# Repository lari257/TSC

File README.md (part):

### Florea Larisa - 333CA

# eBook Reader

## Diagrama Bloc

[Diagrama](https://www.mermaidchart.com/raw/8d10b74d-7767-4ccb-a096-3764c8156505?theme=light&version=v0.1&format=svg)

## Bill Of Materials (BOM)

| Part         | Value                         | Device                                     | Footprint Name                          | Detailed Description                                                                                                                   | CHECK_PRICES                                                                                                            | DATASHEET                                                                                                                   |
|--------------|-------------------------------|--------------------------------------------|-----------------------------------------|----------------------------------------------------------------------------------------------------------------------------------------|-------------------------------------------------------------------------------------------------------------------------|------------------------------------------------------------------------------------------------------------------------------|
| C1           | 4.7uF                         | EAGLE-LTSPICE_CC0402                         | EAGLE-LTSPICE_C0402                         | CAPACITOR, European symbol                                                                                                             | [Link](https://ro.mouser.com/ProductDetail/EPCOS-TDK/B72520T0350K062?qs=dEfas%2FXlABIszF52uu7vrg%3D%3D)                                                                                                                     | nan                                                                                                                          |
| C1_BAT2      | 4.7uF                         | EAGLE-LTSPICE_CC0402                         | EAGLE-LTSPICE_C0402                         | CAPACITOR, European symbol                                                                                                             | [Link](https://ro.mouser.com/ProductDetail/EPCOS-TDK/B72520T0350K062?qs=dEfas%2FXlABIszF52uu7vrg%3D%3D)                                                                                                                       | nan                                                                                                                          |
| C2           | 100nF                         | ESP32_WROVER_EAGLE-LTSPICE_CC0402            | ESP32_WROVER_EAGLE-LTSPICE_C0402            | CAPACITOR, European symbol                                                                                                             | [Link](https://componentsearchengine.com/part-view/CC0402MRX5R5BB106/YAGEO)                                                                                                                    | nan                                                                                                                          |
| C2_BAT      | 4.7uF                         | ESP32_WROVER_EAGLE-LTSPICE_CC0402            | ESP32_WROVER_EAGLE-LTSPICE_C0402            | CAPACITOR, European symbol                                                                                                             | [Link](https://componentsearchengine.com/part-view/CC0402MRX5R5BB106/YAGEO)                                                                                                                      | nan                                                                                                                          |
| C3           | 100uF TANT                    | RCL_CPOL-EUCT3528                          | RCL_CT3528                          | POLARIZED CAPACITOR, European symbol                                                                                                   | [Link](https://eu.mouser.com/ProductDetail/KYOCERA-AVX/F910J107MBAAJ6?qs=PqoDHHvF649LraCA%2FjeGXg%3D%3D)                        | [datasheet](https://ro.mouser.com/datasheet/2/40/F91_AJ6-3162641.pdf)                                                                     |
| C4           | 4.7uF/25V                     | ESP32_WROVER_EAGLE-LTSPICE_CC0402            | ESP32_WROVER_EAGLE-LTSPICE_C0402            | CAPACITOR, European symbol                                                                                                             | [Link](https://componentsearchengine.com/part-view/CC0402MRX5R5BB106/YAGEO)                                                                                                                      | nan                                                                                                                          |
| C4_USB       | 100nF                         | ESP32_WROVER_EAGLE-LTSPICE_CC0402            | ESP32_WROVER_EAGLE-LTSPICE_C0402            | CAPACITOR, European symbol                                                                                                             | [Link](https://componentsearchengine.com/part-view/CC0402MRX5R5BB106/YAGEO)                                                                                                                      | nan                                                                                                                          |
| C5           | 1uF                           | ESP32_WROVER_EAGLE-LTSPICE_CC0402            | ESP32_WROVER_EAGLE-LTSPICE_C0402            | CAPACITOR, European symbol                                                                                                             | [Link](https://componentsearchengine.com/part-view/CC0402MRX5R5BB106/YAGEO)                                                                                                                      | nan                                                                                                                          |
| C5_USB       | 4.7uF                        | ESP32_WROVER_EAGLE-LTSPICE_CC0402            | ESP32_WROVER_EAGLE-LTSPICE_C0402            | CAPACITOR, European symbol                                                                                                             | [Link](https://componentsearchengine.com/part-view/CC0402MRX5R5BB106/YAGEO)                                                                                                                      | nan                                                                                                                          |
| C6           | 100nF                         | ESP32_WROVER_EAGLE-LTSPICE_CC0402            | ESP32_WROVER_EAGLE-LTSPICE_C0402            | CAPACITOR, European symbol                                                                                                             | [Link](https://componentsearchengine.com/part-view/CC0402MRX5R5BB106/YAGEO)                                                                                                                      | nan                                                                                                                          |
| C7           | 10uF                          | ESP32_WROVER_EAGLE-LTSPICE_CC0402            | ESP32_WROVER_EAGLE-LTSPICE_C0402            | CAPACITOR, European symbol                                                                                                             | [Link](https://componentsearchengine.com/part-view/CC0402MRX5R5BB106/YAGEO)                                                                                                                     | nan                                                                                                                          |
| C8           | 100nF                         | ESP32_WROVER_EAGLE-LTSPICE_CC0402            | ESP32_WROVER_EAGLE-LTSPICE_C0402            | CAPACITOR, European symbol                                                                                                             | [Link](https://componentsearchengine.com/part-view/CC0402MRX5R5BB106/YAGEO)                                                                                                                      | nan                                                                                                                          |
| C9           | 100nF                         | EAGLE-LTSPICE_CC0402                         | EAGLE-LTSPICE_C0402                         | CAPACITOR, European symbol                                                                                                             | [Link](https://ro.mouser.com/ProductDetail/EPCOS-TDK/B72520T0350K062?qs=dEfas%2FXlABIszF52uu7vrg%3D%3D)                                                                                                                     | nan                                                                                                                          |
| C10          | 100nF                         | ESP32_WROVER_EAGLE-LTSPICE_CC0402            | ESP32_WROVER_EAGLE-LTSPICE_C0402            | CAPACITOR, European symbol                                                                                                             | [Link](https://componentsearchengine.com/part-view/CC0402MRX5R5BB106/YAGEO)                                                                                                                     | nan                                                                                                                          |
| C10_SUPERCAP | CPH3225A                     | CPH3225A                                   | CAPCP3225X100N                           | Cap 0.011F 3.3V 1210 Flat Check availability                                                                                           | [Link](https://www.snapeda.com/parts/CPH3225A/Seiko+Instruments/view-part/?ref=eda)                                               | [datasheet](https://www.snapeda.com/parts/CPH3225A/Seiko%20Instruments/datasheet/)                                                         |
| CHANGE_BUTTON| BUTTON_CUSYOMV1               | BUTTON_CUSYOMV1                            | MYBUTTON                                | nan                                                                                                                                    | [Link](https://industry.panasonic.com/global/en/products/control/switch/light-touch/number/evqpuj02k)                             | [datasheet](https://industry.panasonic.com/global/en/downloads?tab=catalog&small_g_cd=203&part_no=EVQPUJ02K)                               |
| CHG_LED      | nan                           | ADAFRUIT_LEDCHIP-LED0603                     | ADAFRUIT_CHIP-LED0603                     | LED                                                                                                                                    | [Link](https://www.snapeda.com/parts/KP-1608SURCK/Kingbright/view-part/?ref=eda)                                                 | [datasheet](https://www.snapeda.com/parts/KP-1608SURCK/Kingbright/datasheet/)                                                             |
| C_DELAY      | 100nF                         | ESP32_WROVER_EAGLE-LTSPICE_CC0402            | ESP32_WROVER_EAGLE-LTSPICE_C0402            | CAPACITOR, European symbol                                                                                                             | [Link](https://componentsearchengine.com/part-view/CC0402MRX5R5BB106/YAGEO)                                                                                                                     | nan                                                                                                                          |
| D1           | USBLC6-2SC6Y                  | USBLC6-2SC6Y                               | SOT95P280X145-6N                         | Low Cap. ESD Protection Auto SOT-23-6 STMicroelectronics USBLC6-2SC6Y, Dual Uni-Directional TVS Diode Array, 6-Pin SOT-23             | [Link](https://www.snapeda.com/parts/USBLC6-2SC6Y/STMicroelectronics/view-part/?ref=eda)                                           | [datasheet](https://www.snapeda.com/parts/USBLC6-2SC6Y/STMicroelectronics/datasheet/)                                                     |
| D2           | ESP32_WROVER_AVX---SD0805S020S1R0_AVX_SD0805S020S1R0_0_0AVX_SD0805S020S1R0_0_0 | ESP32_WROVER_AVX---SD0805S020S1R0_AVX_SD0805S020S1R0_0_0AVX_SD0805S020S1R0_0_0 | ESP32_WROVER_AVX---SD0805S020S1R0_AVX_SD0805S020S1R0_0 | Schottky Barrier Rectifier Diode                                                                                                       | [Link](https://eu.mouser.com/ProductDetail/KYOCERA-AVX/SD0805S020S1R0?qs=jCA%252BPfw4LHbpkAoSnwrdjw%3D%3D)                        | [datasheet](http://datasheets.avx.com/schottky.pdf)                                                                                        |
| D3           | MBR0530                       | MBR0530                                    | SOD3716X135N                            | ON SEMICONDUCTOR - MBR0530 - DIODE, SCHOTTKY, 0.5A, 30V, SOD-123                                                                        | [Link](https://eu.mouser.com/ProductDetail/KYOCERA-AVX/SD0805S020S1R0?qs=jCA%252BPfw4LHbpkAoSnwrdjw%3D%3D)                        | [datasheet](https://ro.mouser.com/datasheet/2/40/schottky-3165252.pdf)                                                                    |
| D4           | MBR0530                       | MBR0530                                    | SOD3716X135N                            | ON SEMICONDUCTOR - MBR0530 - DIODE, SCHOTTKY, 0.5A, 30V, SOD-123                                                                        | [Link](https://www.snapeda.com/parts/MBR0530/Onsemi/view-part/?ref=eda)                                                            | [datasheet](https://www.snapeda.com/parts/MBR0530/ON%20Semiconductor/datasheet/)                                                           |
| D5           | MBR0530                       | MBR0530                                    | SOD3716X135N                            | ON SEMICONDUCTOR - MBR0530 - DIODE, SCHOTTKY, 0.5A, 30V, SOD-123                                                                        | [Link](https://www.snapeda.com/parts/MBR0530/Onsemi/view-part/?ref=eda)                                                            | [datasheet](https://www.snapeda.com/parts/MBR0530/ON%20Semiconductor/datasheet/)                                                           |
| D6           | PGB1010603MR                  | PGB1010603MR                               | DIOC1608X36N                            | Check availability                                                                                                                     | [Link](https://www.snapeda.com/parts/PGB1010603MR/Littelfuse/view-part/?ref=eda)                                                   | [datasheet](https://www.snapeda.com/parts/PGB1010603MR/Littelfuse%20Inc./datasheet/)                                                       |
| D7           | ESP32_WROVER_AVX---SD0805S020S1R0_AVX_SD0805S020S1R0_0_0AVX_SD0805S020S1R0_0_0 | ESP32_WROVER_AVX---SD0805S020S1R0_AVX_SD0805S020S1R0_0_0AVX_SD0805S020S1R0_0_0 | ESP32_WROVER_AVX---SD0805S020S1R0_AVX_SD0805S020S1R0_0 | Schottky Barrier Rectifier Diode                                                                                                       | [Link](https://eu.mouser.com/ProductDetail/KYOCERA-AVX/SD0805S020S1R0?qs=jCA%252BPfw4LHbpkAoSnwrdjw%3D%3D)                        | [datasheet](http://datasheets.avx.com/schottky.pdf)                                                                                        |
| D8           | PGB1010603MR                  | PGB1010603MR                               | DIOC1608X36N                            | Check availability                                                                                                                     | [Link](https://www.snapeda.com/parts/PGB1010603MR/Littelfuse/view-part/?ref=eda)                                                   | [datasheet](https://www.snapeda.com/parts/PGB1010603MR/Littelfuse%20Inc./datasheet/)                                                       |
| D9           | PGB1010603MR                  | PGB1010603MR                               | DIOC1608X36N                            | Check availability                                                                                                                     | [Link](https://www.snapeda.com/parts/PGB1010603MR/Littelfuse/view-part/?ref=eda)                                                   | [datasheet](https://www.snapeda.com/parts/PGB1010603MR/Littelfuse%20Inc./datasheet/)                                                       |
| D10          | PGB1010603MR                  | PGB1010603MR                               | DIOC1608X36N                            | Check availability                                                                                                                     | [Link](https://www.snapeda.com/parts/PGB1010603MR/Littelfuse/view-part/?ref=eda)                                                   | [datasheet](https://www.snapeda.com/parts/PGB1010603MR/Littelfuse%20Inc./datasheet/)                                                       |
| D11          | PGB1010603MR                  | PGB1010603MR                               | DIOC1608X36N                            | Check availability                                                                                                                     | [Link](https://www.snapeda.com/parts/PGB1010603MR/Littelfuse/view-part/?ref=eda)                                                   | [datasheet](https://www.snapeda.com/parts/PGB1010603MR/Littelfuse%20Inc./datasheet/)                                                       |
| D12          | PGB1010603MR                  | PGB1010603MR                               | DIOC1608X36N                            | Check availability                                                                                                                     | [Link](https://www.snapeda.com/parts/PGB1010603MR/Littelfuse/view-part/?ref=eda)                                                   | [datasheet](https://www.snapeda.com/parts/PGB1010603MR/Littelfuse%20Inc./datasheet/)                                                       |
| EPD_C1       | 1uF/50V                      | ESP32_WROVER_EAGLE-LTSPICE_CC0402            | ESP32_WROVER_EAGLE-LTSPICE_C0402            | CAPACITOR, European symbol                                                                                                             | [Link](https://componentsearchengine.com/part-view/CC0402MRX5R5BB106/YAGEO)                                                                                                                     | [datasheet](http://datasheets.avx.com/schottky.pdf)                                                                                                                          |
| EPD_C2       | 1uF/50V                      | ESP32_WROVER_EAGLE-LTSPICE_CC0402            | ESP32_WROVER_EAGLE-LTSPICE_C0402            | CAPACITOR, European symbol                                                                                                             | [Link](https://componentsearchengine.com/part-view/CC0402MRX5R5BB106/YAGEO)                                                                                                                     | [datasheet](http://datasheets.avx.com/schottky.pdf)                                                                                                                                                           |
| EPD_C5       | 1uF/50V                      | ESP32_WROVER_EAGLE-LTSPICE_CC0402            | ESP32_WROVER_EAGLE-LTSPICE_C0402            | CAPACITOR, European symbol                                                                                                             | [Link](https://componentsearchengine.com/part-view/CC0402MRX5R5BB106/YAGEO)                                                                                                                     | [datasheet](http://datasheets.avx.com/schottky.pdf)                                                                                                                                |
| EPD_C6       | 1uF/50V                      | ESP32_WROVER_EAGLE-LTSPICE_CC0402            | ESP32_WROVER_EAGLE-LTSPICE_C0402            | CAPACITOR, European symbol                                                                                                             | [Link](https://componentsearchengine.com/part-view/CC0402MRX5R5BB106/YAGEO)                                                                                                                     | [datasheet](http://datasheets.avx.com/schottky.pdf)                                                                                                                                |
| EPD_C7       | 1uF/50V                      | ESP32_WROVER_EAGLE-LTSPICE_CC0402            | ESP32_WROVER_EAGLE-LTSPICE_C0402            | CAPACITOR, European symbol                                                                                                             | [Link](https://componentsearchengine.com/part-view/CC0402MRX5R5BB106/YAGEO)                                                                                                                     | [datasheet](http://datasheets.avx.com/schottky.pdf)                                                                                                                               |
| EPD_C8       | 1uF/50V                      | ESP32_WROVER_EAGLE-LTSPICE_CC0402            | ESP32_WROVER_EAGLE-LTSPICE_C0402            | CAPACITOR, European symbol                                                                                                             | [Link](https://componentsearchengine.com/part-view/CC0402MRX5R5BB106/YAGEO)                                                                                                                     | [datasheet](http://datasheets.avx.com/schottky.pdf)                                                                                                                                |
| EPD_C9       | 1uF/50V                      | ESP32_WROVER_EAGLE-LTSPICE_CC0402            | ESP32_WROVER_EAGLE-LTSPICE_C0402            | CAPACITOR, European symbol                                                                                                             | [Link](https://componentsearchengine.com/part-view/CC0402MRX5R5BB106/YAGEO)                                                                                                                     | [datasheet](http://datasheets.avx.com/schottky.pdf)                                                                                                                                |
| EPD_C10      | 1uF/50V                      | ESP32_WROVER_EAGLE-LTSPICE_CC0402            | ESP32_WROVER_EAGLE-LTSPICE_C0402            | CAPACITOR, European symbol                                                                                                             | [Link](https://componentsearchengine.com/part-view/CC0402MRX5R5BB106/YAGEO)                                                                                                                     | [datasheet](http://datasheets.avx.com/schottky.pdf)                                                                                                                                |
| EPD_C11      | 1uF/50V                      | ESP32_WROVER_EAGLE-LTSPICE_CC0402            | ESP32_WROVER_EAGLE-LTSPICE_C0402            | CAPACITOR, European symbol                                                                                                             | [Link](https://componentsearchengine.com/part-view/CC0402MRX5R5BB106/YAGEO)                                                                                                                     | [datasheet](http://datasheets.avx.com/schottky.pdf)                                                                                                                               |
| EPD_C12      | 1uF/50V                      | ESP32_WROVER_EAGLE-LTSPICE_CC0402            | ESP32_WROVER_EAGLE-LTSPICE_C0402            | CAPACITOR, European symbol                                                                                                             | [Link](https://componentsearchengine.com/part-view/CC0402MRX5R5BB106/YAGEO)                                                                                                                     | [datasheet](http://datasheets.avx.com/schottky.pdf)                                                                                                                                |
| IC1          | BD5229G-TR                   | BD5229G-TR                                 | SOT95P280X125-5N                         | Voltage Detector with Adjustable Delay Time: CMOS reset IC, low current consumption, Nch Open Drain and CMOS output types               | [Link](https://componentsearchengine.com/part-view/BD5229G-TR/ROHM%20Semiconductor)                                                | [datasheet](https://analytics.supplyframe.com/trackingservlet/track/?r=0x34EY99PS_gIu2qWuzU9_U842M9-un2szqNoXX0OQ9lqbiEKGN3BJ73jgvlrgiXR89Peb0evqc4GXoUXllBhmfH5FwctZio74NZjIXK4nzRihNQSXdSI3BytPQ01W2mbDl-BrHnDitFFECll9ZQTojC49rQmJNJKdgEcm3aSYjKEsMXPl-eGs-pMLJ6GfjQ2BiKCrz1Zc4X-qzG_VKV2vSzv5P64Ul7Il20ycllQHFjlUO2yTCSMr3lB_jTotw40hK-OEmTdpXx-FpzhJ86P5OvAlgiTQyMiC4Ffnw4yYxkQBVqaiFBg7qrqEqqVSG5v66qM9MTFYImVZ49_rSfStbzcxZuFs4E34nEuhMtfiKeEXX8C4ukc9Dx9NPlTcXcvuyK8oeiAy2ZaZQDfLPj6QFwce4mx7LCqKQZbV9OYmnvPS6jR1oAjYl8BoXRPWUJ15zMhGiMZbVlex-jQFMXW69CJW_IpZKRdsiNKH4ODU_1sqvLLuSSOT8tdE2JjOemnsC60ps8LwboHBeA2g6oA7NNs5-4F5aeZhiCtD42Z5ROwjQ2LlPtjcLlvpGBeHIItUY6A8k3oFuRSm1vUF3wN8_AuXjXENQ3hBxb6uKJO6IWX4DfXH-rBL1GXdAFk5fJeg6UJ1wtLjiR_lA2QrRxQg) |
| IC4          | XC6220A331MR-G               | XC6220A331MR-G                             | SOT95P280X120-5N                         | LDO Voltage Regulators                                                                                                                 | [Link](https://componentsearchengine.com/part-view/XC6220A331MR-G/Torex)                                                      | [datasheet](https://analytics.supplyframe.com/trackingservlet/track/?r=0x34EY99PS_gIu2qWuzU9_U842M9-un2szqNoXX0OQ9lqbiEKGN3BJ73jgvlrgiXR89Peb0evqc4GXoUXllBhmfH5FwctZio74NZjIXK4nyB_3F6n5b2GpxjFkeCFGxjIjl2pAOVy2zcoQGQxuo036k82aGL63A7iug3M0vDx44b9y4q5Rgkc_UTcoUbz-EFKm35u_Pt-UF5-Qq6wcvjqqlBMb2f4RZCO7jxguRPFrgtzlu-fR4ingqEGNbtkagfpmEwtRP5B3cC8Kbx1BcIGKPYw6AweR1OQe9e4kwHfOX0WSJenm7GAt6qfmRfSkY__Bln0SGRQRi7Gb6appE-It2tLEig19WC7b52EeQQlAWpHibjyTqb00F7pqNazdRJYga1x68e32CNZt8xWLj3NfJVDOHS8ZS42zhawi9DWA1aRL3hvdnRcB352G10IL46169qwDsBVTcBHABUmJOZLUiFPAKnU5dw3RkOVJIhv6hb0GJ6_iu4F4MNWLmP2ofAh9emlLrBRmI1lrzpkKKDvQ) |
| J1           | FH34SRJ-24S-0.5SH_99_         | FH34SRJ-24S-0.5SH_99_                       | FH34SRJ24S05SH99                         | 24 Position FFC, FPC Connector Contacts, Top and Bottom 0.020 (0.50mm) Surface Mount, Right Angle                                    | [Link](https://componentsearchengine.com/part-view/XC6220A331MR-G/Torex)                                                      | [datasheet](https://analytics.supplyframe.com/trackingservlet/track/?r=0x34EY99PS_gIu2qWuzU9_U842M9-un2szqNoXX0OQ9lqbiEKGN3BJ73jgvlrgiXR89Peb0evqc4GXoUXllBhmfH5FwctZio74NZjIXK4nyB_3F6n5b2GpxjFkeCFGxjIjl2pAOVy2zcoQGQxuo036k82aGL63A7iug3M0vDx44b9y4q5Rgkc_UTcoUbz-EFKm35u_Pt-UF5-Qq6wcvjqqlBMb2f4RZCO7jxguRPFrgtzlu-fR4ingqEGNbtkagfpmEwtRP5B3cC8Kbx1BcIGKPYw6AweR1OQe9e4kwHfOX0WSJenm7GAt6qfmRfSkY__Bln0SGRQRi7Gb6appE-It2tLEig19WC7b52EeQQlAVZAmjkjl9RSryO-btGBH9xYga1x68e32CNZt8xWLj3NfJVDOHS8ZS42zhawi9DWA1aRL3hvdnRcB352G10IL46169qwDsBVTcBHABUmJOZLUiFPAKnU5dw3RkOVJIhv6hb0GJ6_iu4F4MNWLmP2ofAh9emlLrBRmI1lrzpkKKDvQ) |
| J2           | SAMACSYS_PARTS_USB4110-GF-A   | SAMACSYS_PARTS_USB4110-GF-A                 | SAMACSYS_PARTS_USB4110GFA                 | CONN USB 2.0 TYPE-C R/A SMT                                                                                                            | [Link](https://componentsearchengine.com/part-view/USB4110-GF-A/GCT%20(GLOBAL%20CONNECTOR%20TECHNOLOGY))                        | [datasheet](https://analytics.supplyframe.com/trackingservlet/track/?r=0x34EY99PS_gIu2qWuzU9_U842M9-un2szqNoXX0OQ9lqbiEKGN3BJ73jgvlrgiXR89Peb0evqc4GXoUXllBhmfH5FwctZio74NZjIXK4nzoCi89ZctA4-kDp3BQhkXpH2DzsdO0BvVNaNDstYgXoJP31ecBQz8TbvXGeDXm6lLlGaktv_ZGcnQDXY_Jm4l7qTzZoYvrcDuK6DczS8PHjvO_sLMu5UeAZ8GC7ci13apB0YMahqYRJzrQKert1kdW90QfLJiqmEa800fLodTIaw6Y6Er8Udb1Qer9oaUT73Q0u_seRB1eNyIOWRehwOBjnt5uE3551K46VPpa8BqQGgL8C7WZ9xB_-wXKErpK07VtbRf3EeHwJSoZTlUkLiK1n4ej5DBFkUkQWc_1u9LdksKwxt-NL4Q595A7224xsugtkbEFPk8oOxSGJ_LHYAQAbZcxjTr7-0B2gfKUc0nIgMhHQ1ZmsU-U87OSIrunF4mGuvL05dMNyqXJqtC-uoX003WGaG4kTFpIgyyEskwr4Y4nNs8v65MrOUj8A-o40EQUWDLttvT4qqUpxJw-bbM4kRSPfo2732k6xYzg6g3hisuczWtyDRXRBbx2AzOqNGhOKW6MmYPiwZBj99pIC-1j) |
| J3           | QWIIC_RIGHT_ANGLE             | QWIIC_CONNECTORJS-1MM                       | JST04_1MM_RA                             | SparkFun I2C Standard Qwiic Connector                                                                                                 | [Link](4208%20Adafruit%20\|%20Mouser)                                                                                   | [datasheet](https://www.armega.com.tr/datasheet/4208-adafruit-industries-llc-datasheet-7323652)                                           |
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
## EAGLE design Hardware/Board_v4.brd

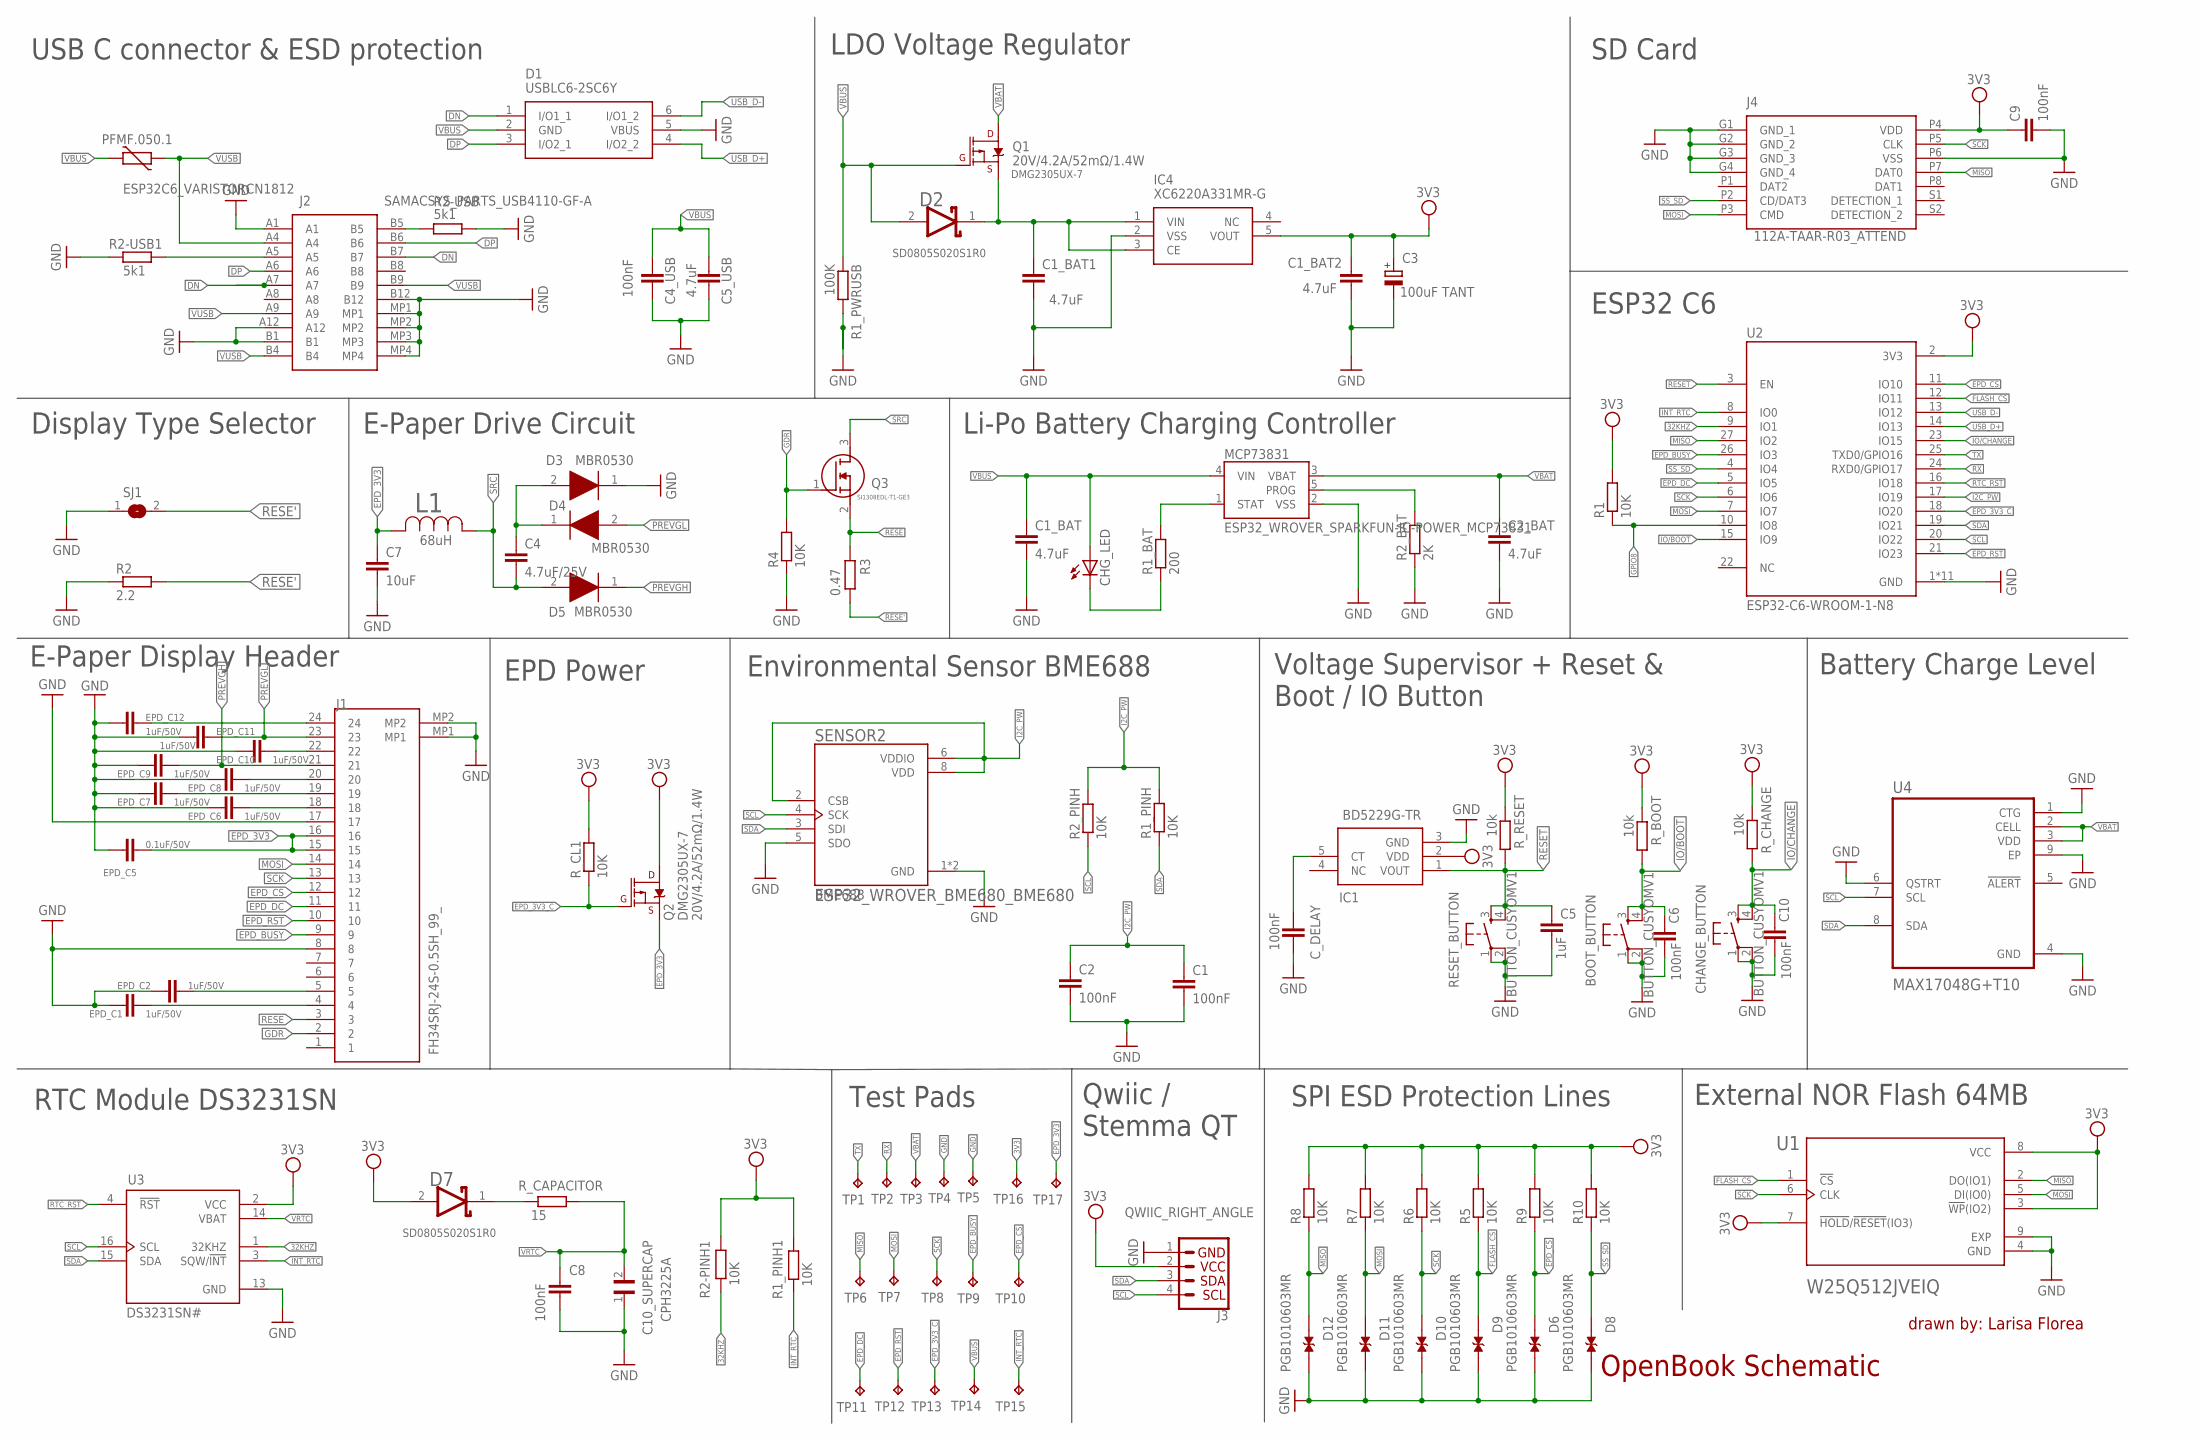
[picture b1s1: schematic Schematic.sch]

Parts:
BOOT_BUTTON: BUTTON_CUSYOMV1; MYBUTTON
C1, C2, C6, C8, C9, C10: 100nF; EAGLE-LTSPICE_C0402
C1_BAT, C2_BAT: 4.7uF; EAGLE-LTSPICE_C0402
C1_BAT1, C1_BAT2, C5_USB: 4.7uF; ESP32_WROVER_EAGLE-LTSPICE_C0402
C3: 100uF TANT; RCL_CT3528
C4: 4.7uF/25V; ESP32_WROVER_EAGLE-LTSPICE_C0402
C4_USB: 100nF; ESP32_WROVER_EAGLE-LTSPICE_C0402
C5: 1uF; EAGLE-LTSPICE_C0402
C7: 10uF; ESP32_WROVER_EAGLE-LTSPICE_C0402
C10_SUPERCAP: CPH3225A; CAPCP3225X100N
CHANGE_BUTTON: BUTTON_CUSYOMV1; MYBUTTON
CHG_LED: ADAFRUIT_LEDCHIP-LED0603; ADAFRUIT_CHIP-LED0603
C_DELAY: 100nF; EAGLE-LTSPICE_C0402
D1: USBLC6-2SC6Y; SOT95P280X145-6N
D2, D7: ESP32_WROVER_AVX---SD0805S020S1R0_AVX_SD0805S020S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; ESP32_WROVER_AVX---SD0805S020S1R0_AVX_SD0805S020S1R0_0
D3, D4, D5: MBR0530; SOD3716X135N
D6, D8, D9, D10, D11, D12: PGB1010603MR; DIOC1608X36N
EPD_C1, EPD_C2, EPD_C6, EPD_C7, EPD_C8, EPD_C9, EPD_C10, EPD_C11, EPD_C12: 1uF/50V; ESP32_WROVER_EAGLE-LTSPICE_C0402
EPD_C5: 0.1uF/50V; ESP32_WROVER_EAGLE-LTSPICE_C0402
IC1: BD5229G-TR; SOT95P280X125-5N
IC4: XC6220A331MR-G; SOT95P280X120-5N
J1: FH34SRJ-24S-0.5SH_99_; FH34SRJ24S05SH99
J2: SAMACSYS_PARTS_USB4110-GF-A; SAMACSYS_PARTS_USB4110GFA
J3: QWIIC_RIGHT_ANGLE; JST04_1MM_RA
J4: 112A-TAAR-R03_ATTEND; 112ATAARR03ATTEND
L1: 744043680IND_4828-WE-TPC_WRE; IND_4828-WE-TPC_WRE
MCP73831: ESP32_WROVER_SPARKFUN-IC-POWER_MCP73831; ESP32_WROVER_SPARKFUN-IC-POWER_SOT23-5
PFMF.050.1: ESP32C6_VARISTORCN1812; ESP32C6_VARISTOR_CT/CN1812
Q1, Q2: 20V/4.2A/52mΩ/1.4W; ESP32_WROVER_SPARKFUN-DISCRETESEMI_SOT23-3
Q3: SI1308EDL-T1-GE3; SOT65P210X110-3N
R1, R1_PINH, R1_PINH1, R2-PINH1, R2_PINH, R4, R5, R6, R7, R8, R9, R10: 10K; ESP32_WROVER_EAGLE-LTSPICE_R0402
R1_BAT: 200; ESP32_WROVER_EAGLE-LTSPICE_R0402
R1_PWRUSB: 100K; ESP32_WROVER_EAGLE-LTSPICE_R0402
R2: 2.2; ESP32_WROVER_EAGLE-LTSPICE_R0402
R2-USB, R2-USB1: 5k1; ESP32_WROVER_EAGLE-LTSPICE_R0402
R2_BAT: 2K; ESP32_WROVER_EAGLE-LTSPICE_R0402
R3: 0.47; ESP32_WROVER_EAGLE-LTSPICE_R0402
RESET_BUTTON: BUTTON_CUSYOMV1; MYBUTTON
R_BOOT: 10k; ESP32_WROVER_EAGLE-LTSPICE_R0402
R_CAPACITOR: 15; ESP32_WROVER_EAGLE-LTSPICE_R0402
R_CHANGE: 10k; ESP32_WROVER_EAGLE-LTSPICE_R0402
R_CL1: 10K; ESP32_WROVER_EAGLE-LTSPICE_R0402
R_RESET: 10k; ESP32_WROVER_EAGLE-LTSPICE_R0402
SENSOR2: ESP32_WROVER_BME680_BME680; ESP32_WROVER_BME680_PSON80P300X300X100-8N
SJ1: SJ
TP1, TP2, TP3, TP4, TP5, TP6, TP7, TP8, TP9, TP10, TP11, TP12, TP13, TP14, TP15, TP16, TP17: TPTP20R; TP20R
U1: W25Q512JVEIQ; SON127P600X800X80-9N
U2: ESP32-C6-WROOM-1-N8; XCVR_ESP32-C6-WROOM-1-N8
U3: DS3231SN#; SOIC127P1032X265-16N
U4: MAX17048G+T10; SON50P200X200X80-9N

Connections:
3V3: C1_BAT2.1, C3.+, C9.1, D7.2 (ANODE), IC1.2 (VDD), IC4.5 (VOUT), J3.2, J4.P4 (VDD), Q2.3 (D), R1.2, R1_PINH1.2, R2-PINH1.2, R5.2, R6.2, R7.2, R8.2, R9.2, R10.2, R_BOOT.1, R_CHANGE.1, R_CL1.2, R_RESET.1, TP16.TP, U1.3 (!WP!(IO2)), U1.7 (!HOLD!/!RESET!(IO3)), U1.8 (VCC), U2.2 (3V3), U3.2 (VCC)
32KHZ: R2-PINH1.1, U2.9 (IO1), U3.1 (32KHZ)
DN: D1.1 (I/O1_1), J2.A7, J2.B7
DP: D1.3 (I/O2_1), J2.A6, J2.B6
EPD_3V3: C7.1, EPD_C5.1, J1.15, J1.16, L1.2, Q2.2 (S), TP17.TP
EPD_3V3_C: Q2.1 (G), R_CL1.1, TP13.TP, U2.18 (IO20)
EPD_BUSY: J1.9, TP9.TP, U2.26 (IO3)
EPD_CS: D6.1, J1.12, R9.1, TP10.TP, U2.11 (IO10)
EPD_DC: J1.11, TP11.TP, U2.5 (IO5)
EPD_RST: J1.10, TP12.TP, U2.21 (IO23)
FLASH_CS: D9.1, R5.1, U1.1 (!CS), U2.12 (IO11)
GDR: J1.2, Q3.1 (G), R4.2
GND: BOOT_BUTTON.1, BOOT_BUTTON.2, C1.2, C1_BAT.2, C1_BAT1.2, C1_BAT2.2, C2.2, C2_BAT.2, C3.-, C4_USB.2, C5.2, C5_USB.2, C6.2, C7.2, C8.2, C9.2, C10.2, C10_SUPERCAP.1, CHANGE_BUTTON.1, CHANGE_BUTTON.2, C_DELAY.2, D1.5 (VBUS), D3.1 (K), D6.2, D8.2, D9.2, D10.2, D11.2, D12.2, EPD_C1.2, EPD_C2.2, EPD_C5.2, EPD_C6.2, EPD_C7.2, EPD_C8.2, EPD_C9.2, EPD_C10.2, EPD_C11.2, EPD_C12.2, IC1.3 (GND), IC4.2 (VSS), J1.8, J1.17, J1.MP1, J1.MP2, J2.A1, J2.A12, J2.B1, J2.B12, J2.MP1, J2.MP2, J2.MP3, J2.MP4, J3.1, J4.G1 (GND_1), J4.G2 (GND_2), J4.G3 (GND_3), J4.G4 (GND_4), J4.P6 (VSS), MCP73831.2 (VSS), R1_PWRUSB.2, R2.1, R2-USB.2, R2-USB1.1, R2_BAT.1, R4.1, RESET_BUTTON.1, RESET_BUTTON.2, SENSOR2.1 (GND), SENSOR2.5 (SDO), SENSOR2.7 (GND), SJ1.1, TP4.TP, TP5.TP, U1.4 (GND), U1.9 (EXP), U2.1 (GND), U2.28 (GND), U2.29_1 (GND), U2.29_2 (GND), U2.29_3 (GND), U2.29_4 (GND), U2.29_5 (GND), U2.29_6 (GND), U2.29_7 (GND), U2.29_8 (GND), U2.29_9 (GND), U3.13 (GND), U4.1 (CTG), U4.4 (GND), U4.6 (QSTRT), U4.9 (EP)
GPIO8: R1.1, U2.10 (IO8)
I2C_PW: C1.1, C2.1, R1_PINH.2, R2_PINH.2, SENSOR2.2 (CSB), SENSOR2.6 (VDDIO), SENSOR2.8 (VDD), U2.17 (IO19)
INT_RTC: R1_PINH1.1, TP15.TP, U2.8 (IO0), U3.3 (SQW/!INT)
IO/BOOT: BOOT_BUTTON.3, BOOT_BUTTON.4, C6.1, R_BOOT.2, U2.15 (IO9)
IO/CHANGE: C10.1, CHANGE_BUTTON.3, CHANGE_BUTTON.4, R_CHANGE.2, U2.23 (IO15)
MISO: D12.1, J4.P7 (DAT0), R8.1, TP6.TP, U1.2 (DO(IO1)), U2.27 (IO2)
MOSI: D11.1, J1.14, J4.P3 (CMD), R7.1, TP7.TP, U1.5 (DI(IO0)), U2.7 (IO7)
unnamed: J2.A5, R2-USB1.2
unnamed: J2.B5, R2-USB.1
unnamed: C1_BAT1.1, D2.1 (CATHODE), IC4.1 (VIN), IC4.3 (CE), Q1.2 (S)
unnamed: CHG_LED.C, R1_BAT.1
unnamed: MCP73831.1 (STAT), R1_BAT.2
unnamed: C4.1, D3.2 (A), D4.1 (K)
unnamed: MCP73831.5 (PROG), R2_BAT.2
unnamed: C_DELAY.1, IC1.5 (CT)
unnamed: D7.1 (CATHODE), R_CAPACITOR.1
unnamed: EPD_C12.1, J1.24
unnamed: EPD_C6.1, J1.18
unnamed: EPD_C7.1, J1.19
unnamed: EPD_C8.1, J1.20
unnamed: EPD_C10.1, J1.22
unnamed: EPD_C2.1, J1.5
unnamed: EPD_C1.1, J1.4
PREVGH: D5.1 (K), EPD_C9.1, J1.21
PREVGL: D4.2 (A), EPD_C11.1, J1.23
RESE: J1.3, Q3.2 (S), R3.2
RESE': R2.2, R3.1, SJ1.2
RESET: C5.1, IC1.1 (VOUT), RESET_BUTTON.3, RESET_BUTTON.4, R_RESET.2, U2.3 (EN)
RTC_RST: U2.16 (IO18), U3.4 (!RST)
RX: TP2.TP, U2.24 (RXD0/GPIO17)
SCK: D10.1, J1.13, J4.P5 (CLK), R6.1, TP8.TP, U1.6 (CLK), U2.6 (IO6)
SCL: J3.4, R2_PINH.1, SENSOR2.4 (SCK), U2.20 (IO22), U3.16 (SCL), U4.7 (SCL)
SDA: J3.3, R1_PINH.1, SENSOR2.3 (SDI), U2.19 (IO21), U3.15 (SDA), U4.8 (SDA)
SRC: C4.2, D5.2 (A), L1.1, Q3.3 (D)
SS_SD: D8.1, J4.P2 (CD/DAT3), R10.1, U2.4 (IO4)
TX: TP1.TP, U2.25 (TXD0/GPIO16)
USB_D+: D1.4 (I/O2_2), U2.14 (IO13)
USB_D-: D1.6 (I/O1_2), U2.13 (IO12)
VBAT: C2_BAT.1, MCP73831.3 (VBAT), Q1.3 (D), TP3.TP, U4.2 (CELL), U4.3 (VDD)
VBUS: C1_BAT.1, C4_USB.1, C5_USB.1, CHG_LED.A, D1.2 (GND), D2.2 (ANODE), MCP73831.4 (VIN), PFMF.050.1.2, Q1.1 (G), R1_PWRUSB.1, TP14.TP
VRTC: C8.1, C10_SUPERCAP.2, R_CAPACITOR.2, U3.14 (VBAT)
VUSB: J2.A4, J2.A9, J2.B4, J2.B9, PFMF.050.1.1

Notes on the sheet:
USB C connector & ESD protection
Display Type Selector
E-Paper Drive Circuit
Li-Po Battery Charging Controller
SD Card
ESP32 C6
EPD Power
Environmental Sensor BME688
Voltage Supervisor + Reset & Boot / IO Button
LDO Voltage Regulator
Battery Charge Level
RTC Module DS3231SN
Test Pads
Qwiic / Stemma QT
SPI ESD Protection Lines
External NOR Flash 64MB
OpenBook Schematic
drawn by: Larisa Florea
E-Paper Display Header

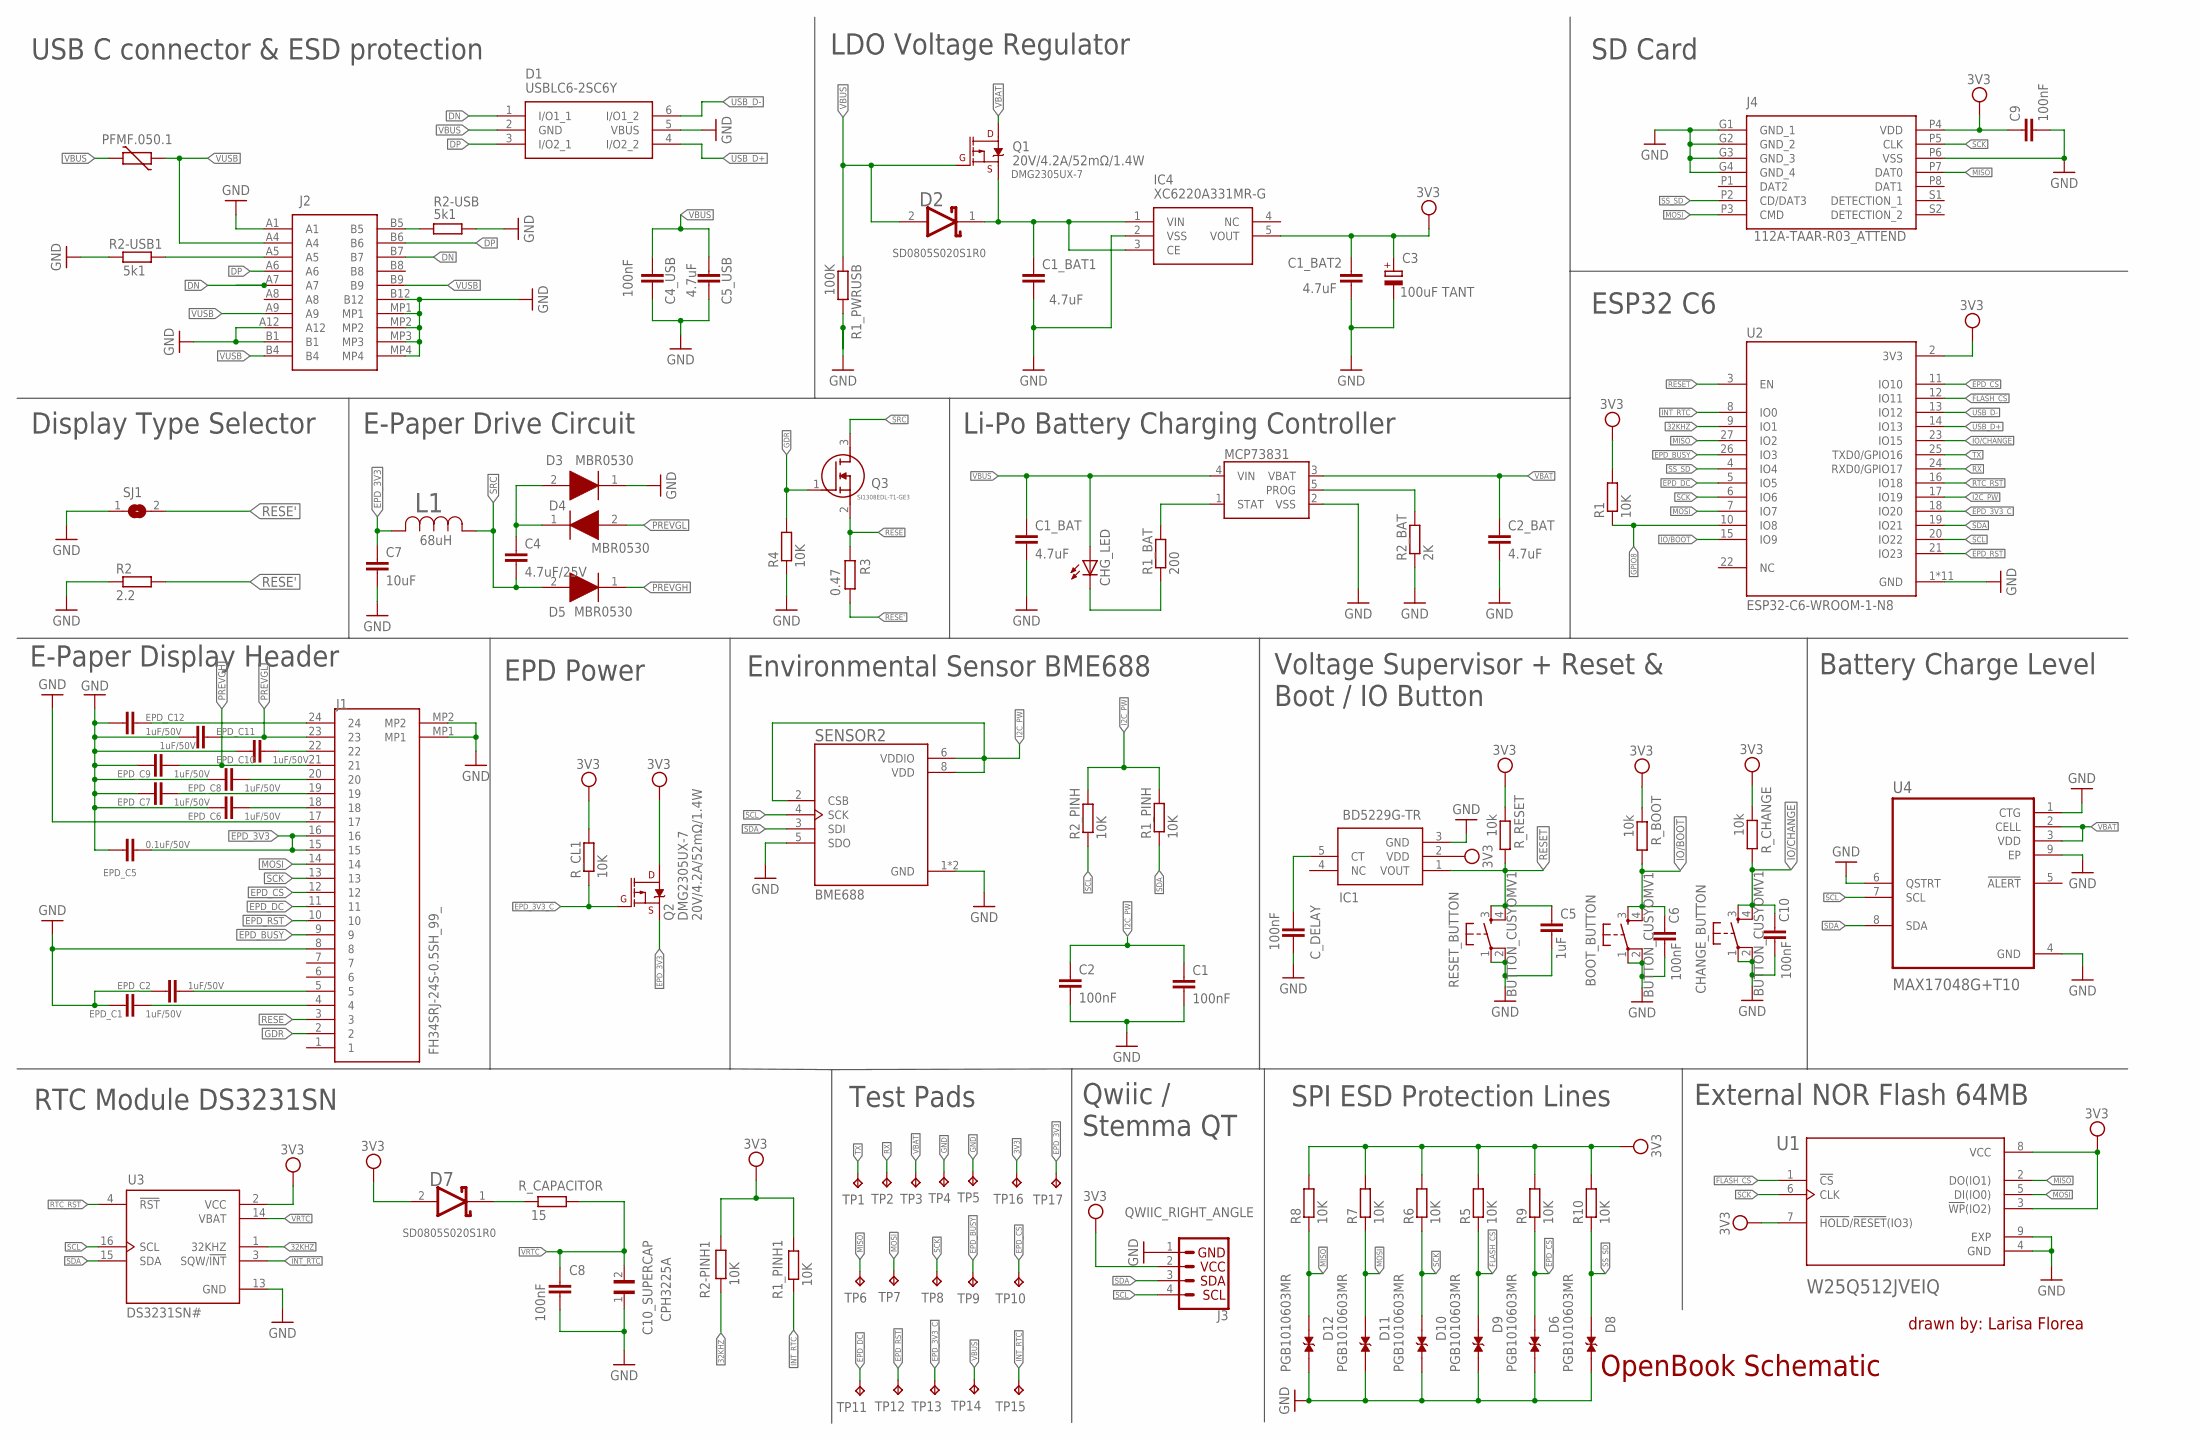
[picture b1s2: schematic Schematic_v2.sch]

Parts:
BOOT_BUTTON: BUTTON_CUSYOMV1; MYBUTTON
C1, C2, C6, C8, C9, C10: 100nF; EAGLE-LTSPICE_C0402
C1_BAT, C2_BAT: 4.7uF; EAGLE-LTSPICE_C0402
C1_BAT1, C1_BAT2, C5_USB: 4.7uF; ESP32_WROVER_EAGLE-LTSPICE_C0402
C3: 100uF TANT; RCL_CT3528
C4: 4.7uF/25V; ESP32_WROVER_EAGLE-LTSPICE_C0402
C4_USB: 100nF; ESP32_WROVER_EAGLE-LTSPICE_C0402
C5: 1uF; EAGLE-LTSPICE_C0402
C7: 10uF; ESP32_WROVER_EAGLE-LTSPICE_C0402
C10_SUPERCAP: CPH3225A; CAPCP3225X100N
CHANGE_BUTTON: BUTTON_CUSYOMV1; MYBUTTON
CHG_LED: ADAFRUIT_LEDCHIP-LED0603; ADAFRUIT_CHIP-LED0603
C_DELAY: 100nF; EAGLE-LTSPICE_C0402
D1: USBLC6-2SC6Y; SOT95P280X145-6N
D2, D7: ESP32_WROVER_AVX---SD0805S020S1R0_AVX_SD0805S020S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; ESP32_WROVER_AVX---SD0805S020S1R0_AVX_SD0805S020S1R0_0
D3, D4, D5: MBR0530; SOD3716X135N
D6, D8, D9, D10, D11, D12: PGB1010603MR; DIOC1608X36N
EPD_C1, EPD_C2, EPD_C6, EPD_C7, EPD_C8, EPD_C9, EPD_C10, EPD_C11, EPD_C12: 1uF/50V; ESP32_WROVER_EAGLE-LTSPICE_C0402
EPD_C5: 0.1uF/50V; ESP32_WROVER_EAGLE-LTSPICE_C0402
IC1: BD5229G-TR; SOT95P280X125-5N
IC4: XC6220A331MR-G; SOT95P280X120-5N
J1: FH34SRJ-24S-0.5SH_99_; FH34SRJ24S05SH99
J2: SAMACSYS_PARTS_USB4110-GF-A; SAMACSYS_PARTS_USB4110GFA
J3: QWIIC_RIGHT_ANGLE; JST04_1MM_RA
J4: 112A-TAAR-R03_ATTEND; 112ATAARR03ATTEND
L1: 744043680IND_4828-WE-TPC_WRE; IND_4828-WE-TPC_WRE
MCP73831: ESP32_WROVER_SPARKFUN-IC-POWER_MCP73831; ESP32_WROVER_SPARKFUN-IC-POWER_SOT23-5
PFMF.050.1: ESP32C6_VARISTORCN1812; ESP32C6_VARISTOR_CT/CN1812
Q1, Q2: 20V/4.2A/52mΩ/1.4W; ESP32_WROVER_SPARKFUN-DISCRETESEMI_SOT23-3
Q3: SI1308EDL-T1-GE3; SOT65P210X110-3N
R1, R1_PINH, R1_PINH1, R2-PINH1, R2_PINH, R4, R5, R6, R7, R8, R9, R10: 10K; ESP32_WROVER_EAGLE-LTSPICE_R0402
R1_BAT: 200; ESP32_WROVER_EAGLE-LTSPICE_R0402
R1_PWRUSB: 100K; ESP32_WROVER_EAGLE-LTSPICE_R0402
R2: 2.2; ESP32_WROVER_EAGLE-LTSPICE_R0402
R2-USB, R2-USB1: 5k1; ESP32_WROVER_EAGLE-LTSPICE_R0402
R2_BAT: 2K; ESP32_WROVER_EAGLE-LTSPICE_R0402
R3: 0.47; ESP32_WROVER_EAGLE-LTSPICE_R0402
RESET_BUTTON: BUTTON_CUSYOMV1; MYBUTTON
R_BOOT: 10k; ESP32_WROVER_EAGLE-LTSPICE_R0402
R_CAPACITOR: 15; ESP32_WROVER_EAGLE-LTSPICE_R0402
R_CHANGE: 10k; ESP32_WROVER_EAGLE-LTSPICE_R0402
R_CL1: 10K; ESP32_WROVER_EAGLE-LTSPICE_R0402
R_RESET: 10k; ESP32_WROVER_EAGLE-LTSPICE_R0402
SENSOR2: ESP32_WROVER_BME680_BME680; ESP32_WROVER_BME680_PSON80P300X300X100-8N
SJ1: SJ
TP1, TP2, TP3, TP4, TP5, TP6, TP7, TP8, TP9, TP10, TP11, TP12, TP13, TP14, TP15, TP16, TP17: TPTP20R; TP20R
U1: W25Q512JVEIQ; SON127P600X800X80-9N
U2: ESP32-C6-WROOM-1-N8; XCVR_ESP32-C6-WROOM-1-N8
U3: DS3231SN#; SOIC127P1032X265-16N
U4: MAX17048G+T10; SON50P200X200X80-9N

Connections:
3V3: C1_BAT2.1, C3.+, C9.1, D7.2 (ANODE), IC1.2 (VDD), IC4.5 (VOUT), J3.2, J4.P4 (VDD), Q2.3 (D), R1.2, R1_PINH1.2, R2-PINH1.2, R5.2, R6.2, R7.2, R8.2, R9.2, R10.2, R_BOOT.1, R_CHANGE.1, R_CL1.2, R_RESET.1, TP16.TP, U1.3 (!WP!(IO2)), U1.7 (!HOLD!/!RESET!(IO3)), U1.8 (VCC), U2.2 (3V3), U3.2 (VCC)
32KHZ: R2-PINH1.1, U2.9 (IO1), U3.1 (32KHZ)
DN: D1.1 (I/O1_1), J2.A7, J2.B7
DP: D1.3 (I/O2_1), J2.A6, J2.B6
EPD_3V3: C7.1, EPD_C5.1, J1.15, J1.16, L1.2, Q2.2 (S), TP17.TP
EPD_3V3_C: Q2.1 (G), R_CL1.1, TP13.TP, U2.18 (IO20)
EPD_BUSY: J1.9, TP9.TP, U2.26 (IO3)
EPD_CS: D6.1, J1.12, R9.1, TP10.TP, U2.11 (IO10)
EPD_DC: J1.11, TP11.TP, U2.5 (IO5)
EPD_RST: J1.10, TP12.TP, U2.21 (IO23)
FLASH_CS: D9.1, R5.1, U1.1 (!CS), U2.12 (IO11)
GDR: J1.2, Q3.1 (G), R4.2
GND: BOOT_BUTTON.1, BOOT_BUTTON.2, C1.2, C1_BAT.2, C1_BAT1.2, C1_BAT2.2, C2.2, C2_BAT.2, C3.-, C4_USB.2, C5.2, C5_USB.2, C6.2, C7.2, C8.2, C9.2, C10.2, C10_SUPERCAP.1, CHANGE_BUTTON.1, CHANGE_BUTTON.2, C_DELAY.2, D1.5 (VBUS), D3.1 (K), D6.2, D8.2, D9.2, D10.2, D11.2, D12.2, EPD_C1.2, EPD_C2.2, EPD_C5.2, EPD_C6.2, EPD_C7.2, EPD_C8.2, EPD_C9.2, EPD_C10.2, EPD_C11.2, EPD_C12.2, IC1.3 (GND), IC4.2 (VSS), J1.8, J1.17, J1.MP1, J1.MP2, J2.A1, J2.A12, J2.B1, J2.B12, J2.MP1, J2.MP2, J2.MP3, J2.MP4, J3.1, J4.G1 (GND_1), J4.G2 (GND_2), J4.G3 (GND_3), J4.G4 (GND_4), J4.P6 (VSS), MCP73831.2 (VSS), R1_PWRUSB.2, R2.1, R2-USB.2, R2-USB1.1, R2_BAT.1, R4.1, RESET_BUTTON.1, RESET_BUTTON.2, SENSOR2.1 (GND), SENSOR2.5 (SDO), SENSOR2.7 (GND), SJ1.1, TP4.TP, TP5.TP, U1.4 (GND), U1.9 (EXP), U2.1 (GND), U2.28 (GND), U2.29_1 (GND), U2.29_2 (GND), U2.29_3 (GND), U2.29_4 (GND), U2.29_5 (GND), U2.29_6 (GND), U2.29_7 (GND), U2.29_8 (GND), U2.29_9 (GND), U3.13 (GND), U4.1 (CTG), U4.4 (GND), U4.6 (QSTRT), U4.9 (EP)
GPIO8: R1.1, U2.10 (IO8)
I2C_PW: C1.1, C2.1, R1_PINH.2, R2_PINH.2, SENSOR2.2 (CSB), SENSOR2.6 (VDDIO), SENSOR2.8 (VDD), U2.17 (IO19)
INT_RTC: R1_PINH1.1, TP15.TP, U2.8 (IO0), U3.3 (SQW/!INT)
IO/BOOT: BOOT_BUTTON.3, BOOT_BUTTON.4, C6.1, R_BOOT.2, U2.15 (IO9)
IO/CHANGE: C10.1, CHANGE_BUTTON.3, CHANGE_BUTTON.4, R_CHANGE.2, U2.23 (IO15)
MISO: D12.1, J4.P7 (DAT0), R8.1, TP6.TP, U1.2 (DO(IO1)), U2.27 (IO2)
MOSI: D11.1, J1.14, J4.P3 (CMD), R7.1, TP7.TP, U1.5 (DI(IO0)), U2.7 (IO7)
unnamed: J2.A5, R2-USB1.2
unnamed: J2.B5, R2-USB.1
unnamed: C1_BAT1.1, D2.1 (CATHODE), IC4.1 (VIN), IC4.3 (CE), Q1.2 (S)
unnamed: CHG_LED.C, R1_BAT.1
unnamed: MCP73831.1 (STAT), R1_BAT.2
unnamed: C4.1, D3.2 (A), D4.1 (K)
unnamed: MCP73831.5 (PROG), R2_BAT.2
unnamed: C_DELAY.1, IC1.5 (CT)
unnamed: D7.1 (CATHODE), R_CAPACITOR.1
unnamed: EPD_C12.1, J1.24
unnamed: EPD_C6.1, J1.18
unnamed: EPD_C7.1, J1.19
unnamed: EPD_C8.1, J1.20
unnamed: EPD_C10.1, J1.22
unnamed: EPD_C2.1, J1.5
unnamed: EPD_C1.1, J1.4
PREVGH: D5.1 (K), EPD_C9.1, J1.21
PREVGL: D4.2 (A), EPD_C11.1, J1.23
RESE: J1.3, Q3.2 (S), R3.2
RESE': R2.2, R3.1, SJ1.2
RESET: C5.1, IC1.1 (VOUT), RESET_BUTTON.3, RESET_BUTTON.4, R_RESET.2, U2.3 (EN)
RTC_RST: U2.16 (IO18), U3.4 (!RST)
RX: TP2.TP, U2.24 (RXD0/GPIO17)
SCK: D10.1, J1.13, J4.P5 (CLK), R6.1, TP8.TP, U1.6 (CLK), U2.6 (IO6)
SCL: J3.4, R2_PINH.1, SENSOR2.4 (SCK), U2.20 (IO22), U3.16 (SCL), U4.7 (SCL)
SDA: J3.3, R1_PINH.1, SENSOR2.3 (SDI), U2.19 (IO21), U3.15 (SDA), U4.8 (SDA)
SRC: C4.2, D5.2 (A), L1.1, Q3.3 (D)
SS_SD: D8.1, J4.P2 (CD/DAT3), R10.1, U2.4 (IO4)
TX: TP1.TP, U2.25 (TXD0/GPIO16)
USB_D+: D1.4 (I/O2_2), U2.14 (IO13)
USB_D-: D1.6 (I/O1_2), U2.13 (IO12)
VBAT: C2_BAT.1, MCP73831.3 (VBAT), Q1.3 (D), TP3.TP, U4.2 (CELL), U4.3 (VDD)
VBUS: C1_BAT.1, C4_USB.1, C5_USB.1, CHG_LED.A, D1.2 (GND), D2.2 (ANODE), MCP73831.4 (VIN), PFMF.050.1.2, Q1.1 (G), R1_PWRUSB.1, TP14.TP
VRTC: C8.1, C10_SUPERCAP.2, R_CAPACITOR.2, U3.14 (VBAT)
VUSB: J2.A4, J2.A9, J2.B4, J2.B9, PFMF.050.1.1

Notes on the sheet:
USB C connector & ESD protection
Display Type Selector
E-Paper Drive Circuit
Li-Po Battery Charging Controller
SD Card
ESP32 C6
EPD Power
Environmental Sensor BME688
Voltage Supervisor + Reset & Boot / IO Button
LDO Voltage Regulator
Battery Charge Level
RTC Module DS3231SN
Test Pads
Qwiic / Stemma QT
SPI ESD Protection Lines
External NOR Flash 64MB
OpenBook Schematic
drawn by: Larisa Florea
E-Paper Display Header

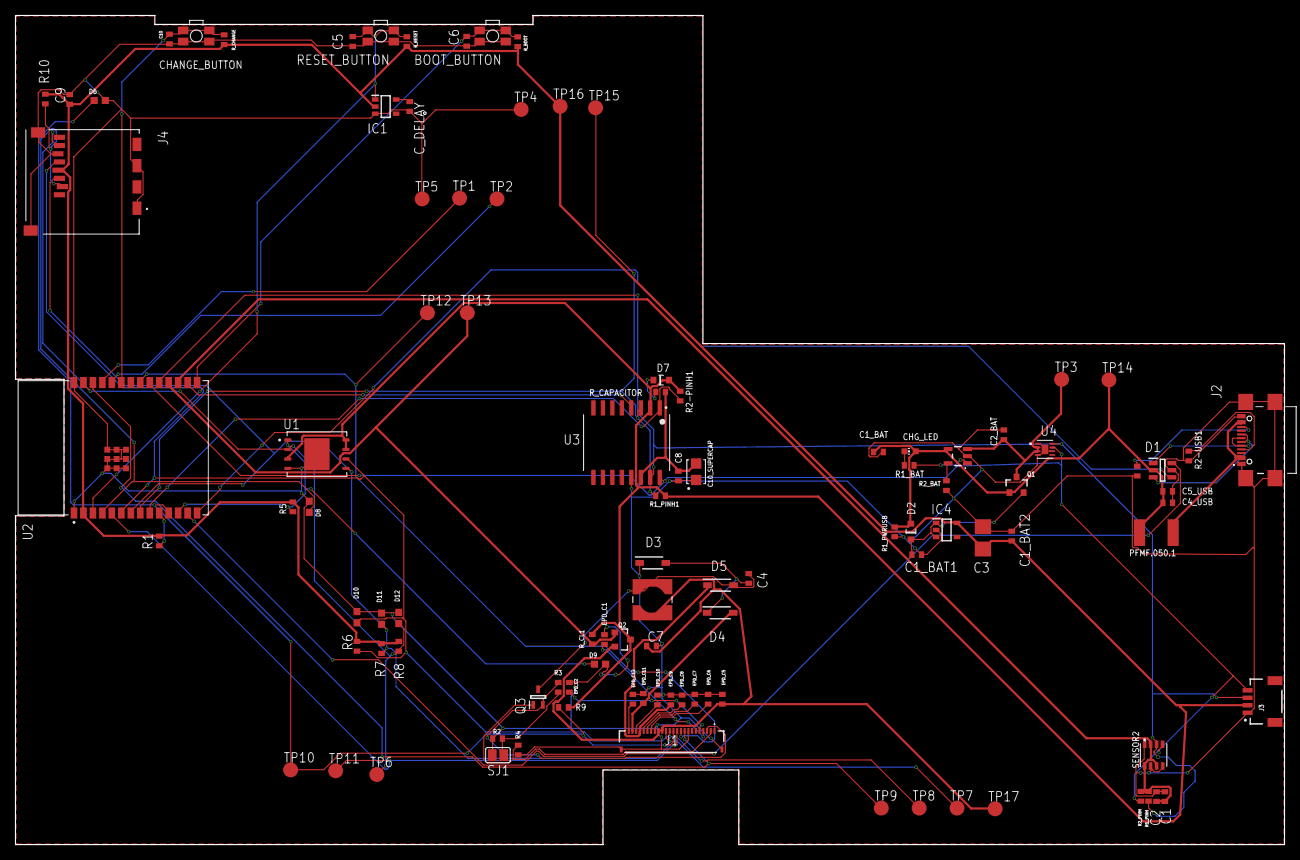
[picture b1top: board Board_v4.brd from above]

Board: 2 copper layers, 170.2 x 111.2 mm, 103 parts (0 on the bottom side), 55 nets.

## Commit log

2025-04-06 Create LICENSE
2025-04-06 Create ddd
2025-04-06 Create ll
2025-04-06 Create lll
2025-04-06 exploaded view
2025-04-06 images
2025-04-13 add exploded view

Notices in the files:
parts and their libraries:
COPYRIGHT: Copyright (C) 2024 Ultra Librarian. All rights reserved.
